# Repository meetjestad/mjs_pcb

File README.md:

Meetjestad PCB repository
=========================

This repository contains various versions of the sensor station PCB used
by [Meetjestad](https://www.meetjestad.net).

The easiest way to see the various version is to have a look at the
releases on Github, which are tagged with the version number. The
release pages also contain rendered (PDF) schematics and board files.

Software
--------
These boards can be programmed using the Arduino environment. The
necessary configuration and support files to allow this, along with
instructions can be found in the [mjs_boards
repository](https://github.com/meetjestad/mjs_boards).

The firmware typically used on these boards is published in the
[mjs_firmware repository](https://github.com/meetjestad/mjs_firmware)
(mjs2020 branch for the MJS2020 board).

License
-------
The original MJS sensor board is designed by Harmen Zijp, together with
Matthijs Kooijman. The MJS2020 board is partly based on the original
board and is designed by [KITT Engineering](https://www.kitt.nl/en/),
together with Harmen Zijp and Matthijs Kooijman.

The design for both boards is open hardware and licensed
under the the CERN-OHL-W v2 license. Any designs derived from or
containing parts of this design must be similarly licensed. See the
LICENSE file for the full license text.

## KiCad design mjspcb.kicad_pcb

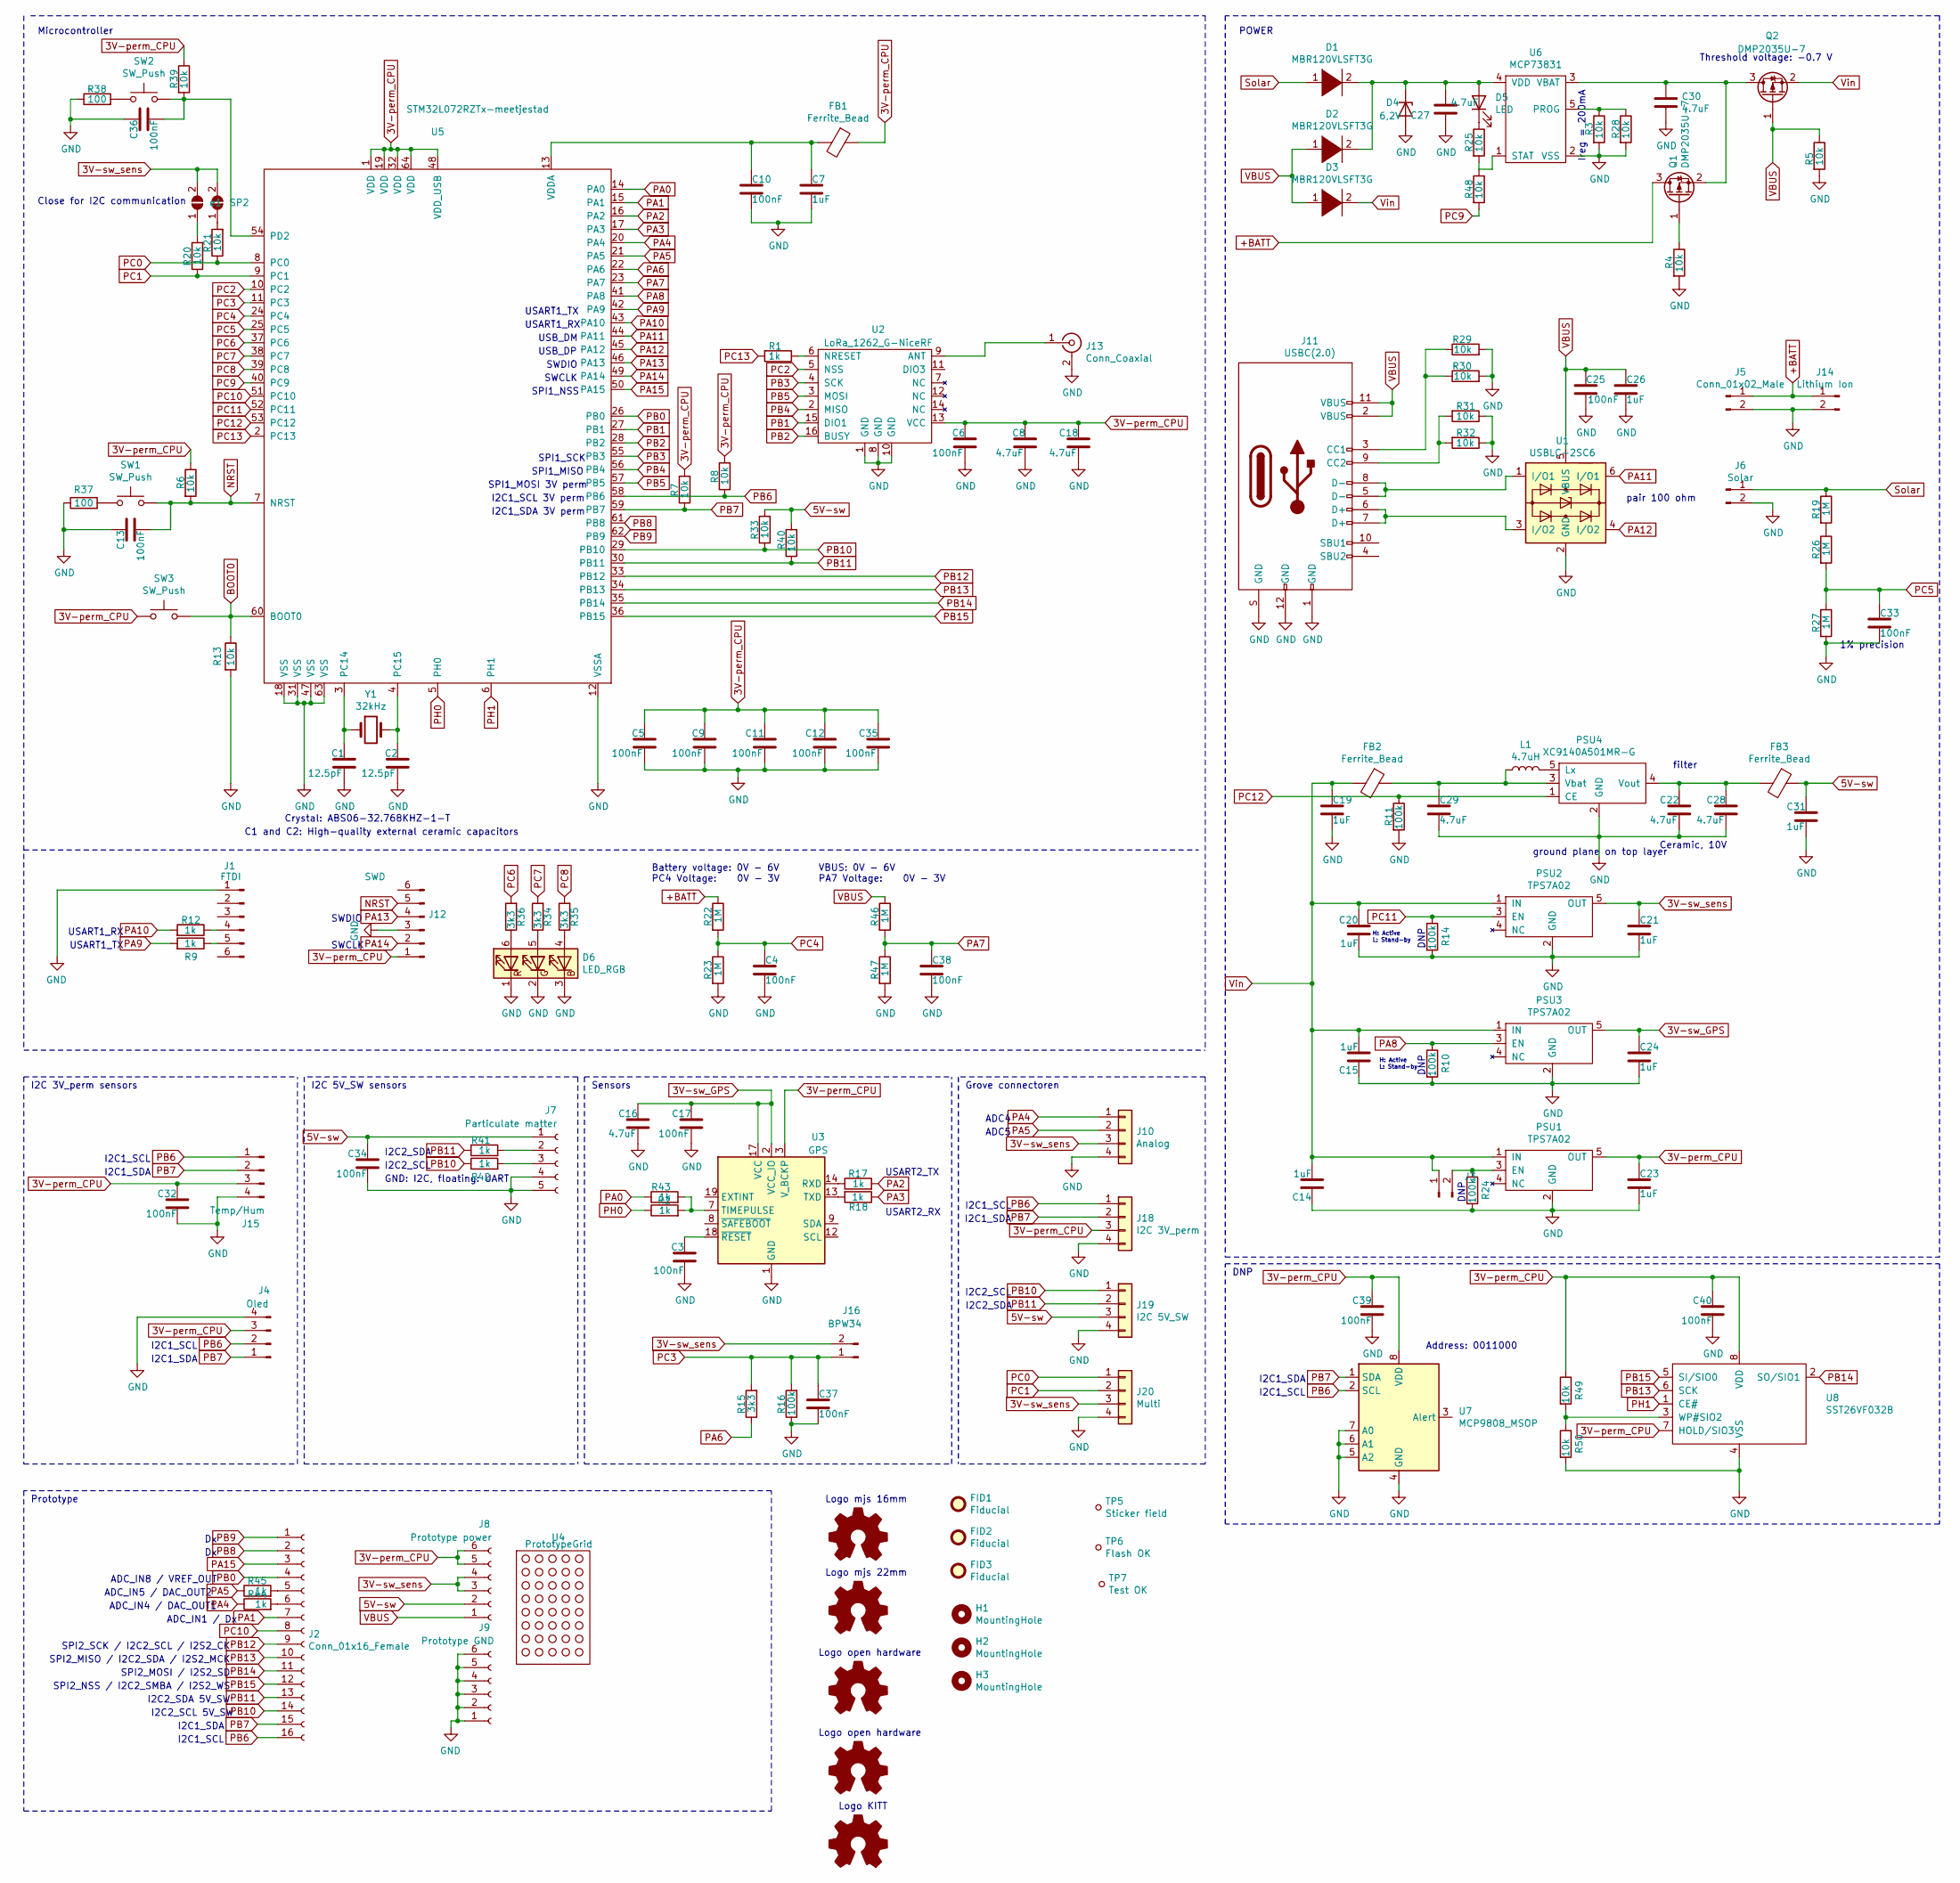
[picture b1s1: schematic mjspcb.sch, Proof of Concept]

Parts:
C1, C2: 12.5pF; C_0805_2012Metric_Pad1.15x1.40mm_HandSolder
C3, C4, C5, C6, C9, C10, C11, C12, C13, C17, C25, C32, C33, C34, C35, C36, C37, C38, C39, C40: 100nF; C_0805_2012Metric_Pad1.15x1.40mm_HandSolder
C7, C14, C15, C19, C20, C21, C23, C24, C26, C31: 1uF; C_0805_2012Metric_Pad1.15x1.40mm_HandSolder
C8, C16, C18, C22, C27, C28, C29, C30: 4.7uF; C_0805_2012Metric_Pad1.15x1.40mm_HandSolder
D1, D2, D3: MBR120VLSFT3G; Diode_SMD-SOD_123
D4: 6,2V; D_SOD-123
D5: LED; LED_0805_2012Metric
D6: LED_RGB; JTS3535
FB1, FB2, FB3: Ferrite_Bead; R_0805_2012Metric_Pad1.15x1.40mm_HandSolder
FID1, FID2, FID3: Fiducial; Fiducial_0.5mm_Mask1mm
H1, H2, H3: MountingHole; MountingHole_3.2mm_M3
J1: FTDI; PinHeader_1x06_P2.54mm_Vertical
J2: Conn_01x16_Female; PinHeader_Female_1X16
J3: Conn_01x02_Male; PinHeader_Male_1X2
J4: Oled; OLED_1.3
J5: Conn_01x02_Male; Battery__holder
J6: Solar; Combi_2.0_2.45pitch_2PIN
J7: Particulate matter; B5B-ZR
J8: Prototype power; PinHeader_Female_1X6
J9: Prototype GND; PinHeader_Female_1X6
J10: Analog; 2,54_2.0pitchCombi
J11: USBC(2.0); DX07S016JA3R1500
J12: SWD; PinHeader_1x06_P2.54mm_Vertical
J13: Conn_Coaxial; SMA connector edge mount
J14: Lithium Ion; Combi_2.0_2.45pitch_2PIN
J15: Temp/Hum; SI7021
J16: BPW34; PinHeader_Male_1X2
J18: I2C 3V_perm; 2,54_2.0pitchCombi
J19: I2C 5V_SW; 2,54_2.0pitchCombi
J20: Multi; 2,54_2.0pitchCombi
L1: 4.7uH; R_0805_2012Metric_Pad1.15x1.40mm_HandSolder
Logo_kitt1: Logo_Open_Hardware_Small; Kitt_logo
Logo_mjs1: Logo_Open_Hardware_Small; mjs-logo-16mm
Logo_mjs2, Logo_mjs4: Logo_Open_Hardware_Small; OSHW-Logo2_7.3x6mm_SilkScreen
Logo_mjs3: Logo_Open_Hardware_Small; mjs-logo-22mm
PSU1, PSU2, PSU3: TPS7A02; SOT-23-5_HandSoldering
PSU4: XC9140A501MR-G; SOT-23-5_HandSoldering
Q1, Q2: DMP2035U-7; SOT-23
R1, R2, R9, R12, R17, R18, R41, R42, R43, R44, R45: 1k; R_0805_2012Metric_Pad1.15x1.40mm_HandSolder
R3, R4, R5, R6, R7, R8, R13, R20, R21, R25, R28, R29, R30, R31, R32, R33, R39, R40, R48, R49, R50: 10k; R_0805_2012Metric_Pad1.15x1.40mm_HandSolder
R10, R11, R14, R16, R24: 100k; R_0805_2012Metric_Pad1.15x1.40mm_HandSolder
R15, R34, R35, R36: 3k3; R_0805_2012Metric_Pad1.15x1.40mm_HandSolder
R19, R22, R23, R26, R27, R46, R47: 1M; R_0805_2012Metric_Pad1.15x1.40mm_HandSolder
R37, R38: 100; R_0805_2012Metric_Pad1.15x1.40mm_HandSolder
SP2: SolderJumper_2_Open; SolderJumper-2_P1.3mm_Bridged_RoundedPad1.0x1.5mm
SW1, SW2: SW_Push; SW_Push_6mm
SW3: SW_Push; Switch_Header2.54_Combi
TP5: Sticker field
TP6: Flash OK
TP7: Test OK
U1: USBLC-2SC6; SOT-23-6_Handsoldering
U2: LoRa_1262_G-NiceRF
U3: GPS; GPS_ublox-SAM-M8Q
U4: PrototypeGrid; Prototype grid
U5: STM32L072RZTx-meetjestad; STM32F072_LQFP-64
U6: MCP73831; SOT-23-5_HandSoldering
U7: MCP9808_MSOP; MSOP-8_3x3mm_P0.65mm
U8: SST26VF032B; SOIJ-8_5.3x5.3mm_P1.27mm
Y1: 32kHz; R_0805_2012Metric_Pad1.15x1.40mm_HandSolder
e1: SolderJumper_2_Open; SolderJumper-2_P1.3mm_Bridged_RoundedPad1.0x1.5mm

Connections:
3V-perm_CPU: C5.1, C6.1, C8.1, C9.1, C11.1, C12.1, C18.1, C23.1, C32.2, C35.1, C39.2, C40.2, FB1.1, J4.3, J8.5, J8.6, J12.1, J15.3, J18.3, PSU1.5 (OUT), R6.1, R7.2, R8.2, R39.1, R49.1, SW3.1, U2.13 (VCC), U3.3 (V_BCKP), U5.1 (VDD), U5.19 (VDD), U5.32 (VDD), U5.48 (VDD_USB), U5.64 (VDD), U7.8 (VDD), U8.7 (HOLD/SIO3), U8.8 (VDD)
3V-sw_GPS: C16.1, C17.1, C24.1, PSU3.5 (OUT), U3.2 (VCC_IO), U3.17 (VCC)
3V-sw_sens: C21.1, J8.3, J8.4, J10.3, J16.2, J20.3, PSU2.5 (OUT), SP2.2 (B), e1.2 (B); also elsewhere on the board
5V-sw: C31.1, C34.2, FB3.1, J7.1, J8.2, J19.3, R33.2, R40.2
+BATT: J5.1, J14.1, Q1.3 (D), R22.1
BOOT0: R13.1, SW3.2, U5.60 (BOOT0)
GND: C1.2, C2.2, C3.1, C4.2, C5.2, C6.2, C7.2, C8.2, C9.2, C10.2, C11.2, C12.2, C13.2, C14.1, C15.1, C16.2, C17.2, C18.2, C19.2, C20.1, C21.2, C22.2, C23.2, C24.2, C25.1, C26.2, C27.1, C28.2, C29.2, C30.2, C31.2, C32.1, C33.2, C34.1, C35.2, C36.2, C37.2, C38.2, C39.1, C40.1, D4.2 (A), D6.1 (RK), D6.2 (GK), D6.3 (BK), J1.1, J4.4, J5.2, J6.2, J7.4, J7.5, J9.1, J9.2, J9.3, J9.4, J9.5, J9.6, J10.4, J11.1 (GND), J11.12 (GND), J11.S (GND), J12.3, J13.2 (Ext), J14.2, J15.4, J18.4, J19.4, J20.4, PSU1.2 (GND), PSU2.2 (GND), PSU3.2 (GND), PSU4.2 (GND), R3.2, R4.2, R5.2, R10.2, R11.2, R13.2, R14.2, R16.1, R23.2, R24.2, R27.2, R28.2, R29.2, R30.2, R31.1, R32.1, R37.1, R38.1, R47.2, R50.2, U1.2 (GND), U2.1 (GND), U2.8 (GND), U2.10 (GND), U3.1 (GND), U3.4 (GND), U3.5 (GND), U3.6 (GND), U3.10 (GND), U3.11 (GND), U3.15 (GND), U3.16 (GND), U3.20 (GND), U5.12 (VSSA), U5.18 (VSS), U5.31 (VSS), U5.47 (VSS), U5.63 (VSS), U6.2 (VSS), U7.4 (GND), U7.5 (A2), U7.6 (A1), U7.7 (A0), U8.4 (VSS)
NRST: C13.1, J12.5, R6.2, SW1.2, U5.7 (NRST)
unnamed: C1.1, U5.3 (PC14), Y1.1
unnamed: C2.1, U5.4 (PC15), Y1.2
unnamed: C3.2, U3.18 (~RESET)
unnamed: C7.1, C10.1, FB1.2, U5.13 (VDDA)
unnamed: C22.1, C28.1, FB3.2, PSU4.4 (Vout)
unnamed: C27.2, D1.2 (A), D2.2 (A), D4.1 (K), D5.2 (A), U6.4 (VDD)
unnamed: C29.1, FB2.1, L1.1, PSU4.3 (Vbat)
unnamed: C30.1, Q1.2 (S), Q2.3 (D), U6.3 (VBAT)
unnamed: C36.1, R39.2, SW2.2, U5.54 (PD2)
unnamed: D5.1 (K), R25.1
unnamed: D6.4 (BA), R35.1
unnamed: D6.5 (GA), R34.1
unnamed: D6.6 (RA), R36.1
unnamed: J1.4, R12.1
unnamed: J1.5, R9.1
unnamed: J2.5, R45.2
unnamed: J2.6, R44.2
unnamed: J3.2, PSU1.3 (EN), R24.1
unnamed: J7.2, R41.2
unnamed: J7.3, R42.2
unnamed: J11.3 (CC1), R29.1, R30.1
unnamed: J11.5 (D-), J11.8 (D-), U1.1 (I/O1)
unnamed: J11.6 (D+), J11.7 (D+), U1.3 (I/O2)
unnamed: J11.9 (CC2), R31.2, R32.2
unnamed: J13.1 (In), U2.9 (ANT)
unnamed: L1.2, PSU4.5 (Lx)
unnamed: Q1.1 (G), R4.1
unnamed: R1.1, U2.6 (NRESET)
unnamed: R2.2, R43.2, U3.7 (TIMEPULSE)
unnamed: R17.1, U3.14 (RXD)
unnamed: R18.2, U3.13 (TXD)
unnamed: R19.2, R26.1
unnamed 49: R20.2, e1.1 (A); also elsewhere on the board
unnamed: R21.2, SP2.1 (A)
unnamed: R25.2, R48.1, U6.1 (STAT)
unnamed: R3.1, R28.1, U6.5 (PROG)
unnamed: R37.2, SW1.1
unnamed: R38.2, SW2.1
unnamed: R49.2, R50.1, U8.3 (WP#SIO2)
PA0: R43.1, U5.14 (PA0)
PA1: J2.7, U5.15 (PA1)
PA2: R17.2, U5.16 (PA2)
PA3: R18.1, U5.17 (PA3)
PA4: J10.1, R44.1, U5.20 (PA4)
PA5: J10.2, R45.1, U5.21 (PA5)
PA6: R15.1, U5.22 (PA6)
PA7: C38.1, R46.2, R47.1, U5.23 (PA7)
PA8: PSU3.3 (EN), R10.1, U5.41 (PA8)
PA9: R9.2, U5.42 (PA9)
PA10: R12.2, U5.43 (PA10)
PA11: U1.6 (I/O1), U5.44 (PA11)
PA12: U1.4 (I/O2), U5.45 (PA12)
PA13: J12.4, U5.46 (PA13)
PA14: J12.2, U5.49 (PA14)
PA15: J2.3, U5.50 (PA15)
PB0: J2.4, U5.26 (PB0)
PB1: U2.15 (DIO1), U5.27 (PB1)
PB2: U2.16 (BUSY), U5.28 (PB2)
PB3: U2.4 (SCK), U5.55 (PB3)
PB4: U2.2 (MISO), U5.56 (PB4)
PB5: U2.3 (MOSI), U5.57 (PB5)
PB6: J2.16, J4.2, J15.1, J18.1, R8.1, U5.58 (PB6), U7.2 (SCL)
PB7: J2.15, J4.1, J15.2, J18.2, R7.1, U5.59 (PB7), U7.1 (SDA)
PB8: J2.2, U5.61 (PB8)
PB9: J2.1, U5.62 (PB9)
PB10: J2.14, J19.1, R33.1, R42.1, U5.29 (PB10)
PB11: J2.13, J19.2, R40.1, R41.1, U5.30 (PB11)
PB12: J2.9, U5.33 (PB12)
PB13: J2.10, U5.34 (PB13), U8.6 (SCK)
PB14: J2.11, U5.35 (PB14), U8.2 (SO/SIO1)
PB15: J2.12, U5.36 (PB15), U8.5 (SI/SIO0)
PC0: J20.1, R21.1, U5.8 (PC0)
PC1: J20.2, R20.1, U5.9 (PC1)
PC2: U2.5 (NSS), U5.10 (PC2)
PC3: C37.1, J16.1, R15.2, R16.2, U5.11 (PC3)
PC4: C4.1, R22.2, R23.1, U5.24 (PC4)
PC5: C33.1, R26.2, R27.1, U5.25 (PC5)
PC6: R36.2, U5.37 (PC6)
PC7: R34.2, U5.38 (PC7)
PC8: R35.2, U5.39 (PC8)
PC9: R48.2, U5.40 (PC9)
PC10: J2.8, U5.51 (PC10)
PC11: PSU2.3 (EN), R14.1, U5.52 (PC11)
PC12: PSU4.1 (CE), R11.1, U5.53 (PC12)
PC13: R1.2, U5.2 (PC13)
PH0: R2.1, U5.5 (PH0)
PH1: U5.6 (PH1), U8.1 (CE#)
Solar: D1.1 (K), J6.1, R19.1
VBUS: C25.2, C26.1, D2.1 (K), D3.1 (K), J8.1, J11.2 (VBUS), J11.11 (VBUS), Q2.1 (G), R5.1, R46.1, U1.5 (VBUS)
Vin: C14.2, C15.2, C19.1, C20.2, D3.2 (A), FB2.2, J3.1, PSU1.1 (IN), PSU2.1 (IN), PSU3.1 (IN), Q2.2 (S)

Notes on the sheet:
Microcontroller
C1 and C2: High-quality external ceramic capacitors
Crystal: ABS06-32.768KHZ-1-T
USART1_TX
USART1_RX
SPI1_NSS
SPI1_MISO
SPI1_SCK
USB_DP
USB_DM
SWDIO
SPI1_MOSI 3V perm
I2C1_SCL 3V perm
USART2_TX
USART2_RX
SWCLK
GND: I2C, floating: UART
ADC4
ADC5
Grove connectoren
I2C 5V_SW sensors
I2C2_SDA
I2C 3V_perm sensors
I2C1_SDA 3V perm
I2C1_SCL
I2C1_SDA
I2C2_SCL 5V_SW
I2C2_SDA 5V_SW
I2C2_SCL
ADC_IN1 / Dx
ADC_IN5 / DAC_OUT2
ADC_IN4 / DAC_OUT1
SPI2_MOSI / I2S2_SD
Logo mjs 16mm
Logo open hardware
Logo KITT
Battery voltage: 0V - 6V PC4 Voltage: 0V - 3V
Prototype
Sensors
pair 100 ohm

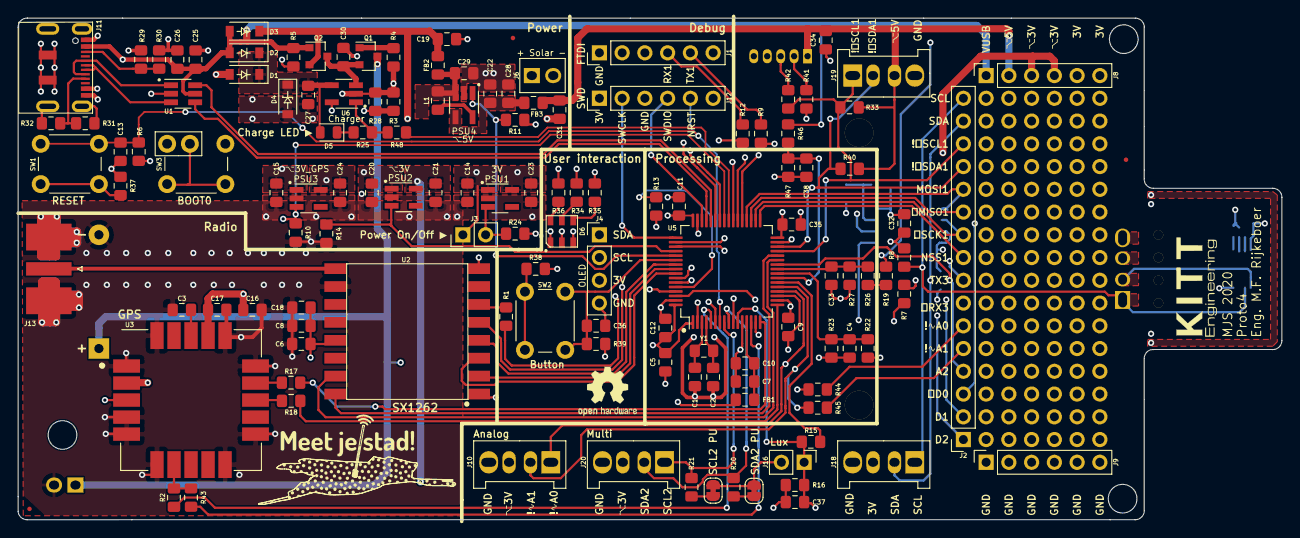
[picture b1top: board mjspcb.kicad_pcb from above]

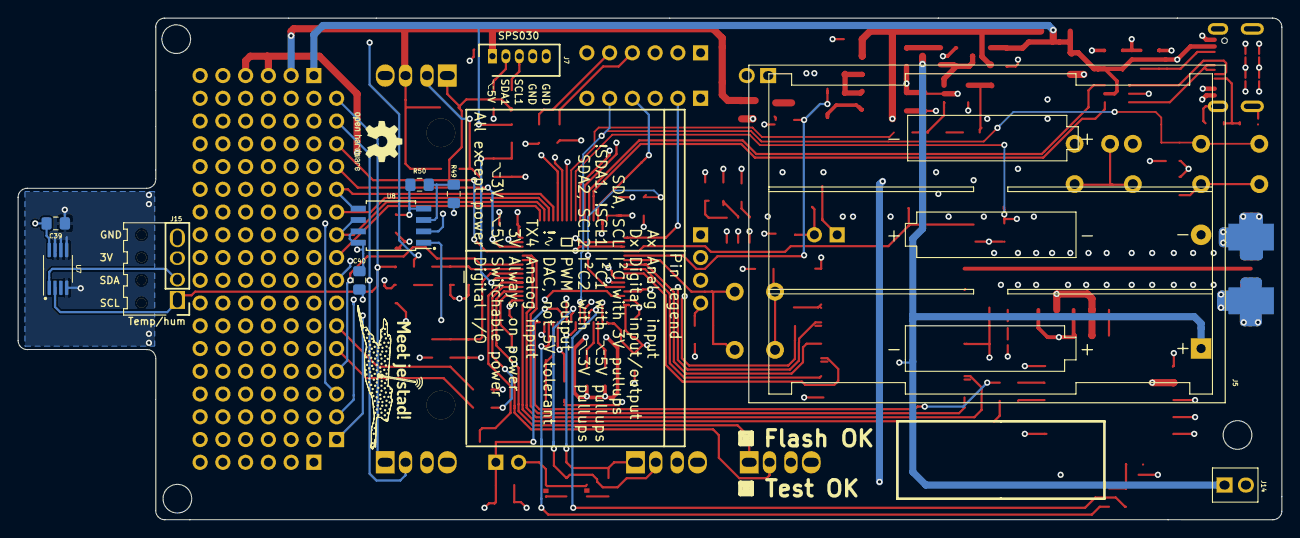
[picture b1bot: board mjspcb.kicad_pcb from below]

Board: 4 copper layers, 141.1 x 56.0 mm, 153 parts (15 on the bottom side), 98 nets.

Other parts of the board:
SP1: SolderJumper_2_Open; SolderJumper-2_P1.3mm_Bridged_RoundedPad1.0x1.5mm

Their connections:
3V-sw_sens: SP1.2; also elsewhere on the board
unnamed 49: SP1.1; also elsewhere on the board

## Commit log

2017-11-07 Revision 2 of Meet je stad PCB
    *added reset header
    *changed pinout of I2C breakout to accomodate Sparkfun Si7021
    *various minor other modifications
2017-11-07 Updated pdf files for PCB revision 2
2018-12-18 Remove build products
    This removes the gerbers, rendered schematics and bom (in various
    format). These will be outdated during development and only really
    relevant for released version, so they are probably better put in a
    release on github rather than in git.
2018-12-18 Convert schematic to KiCad 5
    In KiCad 5, symbols reference the library they are in explicitly. Also,
    a lot of symbols were changed for more consistency. This commit changes
    all symbols to their new version in the official libraries, removing the
    need for our own symbol library (which is removed by this commit).
    For the STU MOSFET component, not specific symbol is available, so a
    generic MOSFET symbol is used instead.
2018-12-18 Delete netlist
    There is no real reason to keep this in git, it is just a temporary file
    between the schema and the layout.
2018-12-18 Replace 2-pin sensor connectors with KK254
    These are latching, polarity protected connectors. This mostly changes
    to silkscreen, though the pads are also slighly differently sized.
2018-12-18 Run a track & via cleanup
2018-12-18 Convert board layout to KiCad 5
    This replaces all footprints with new versions from KiCad 5. Some
    positions and labeling as changed, so this updates everything to match
    the original layout for the most part. Some footprints (barrel jack,
    regulator, battery holder, solder jumpers, perfboard "connector") are
    slightly different. In particualr the battery holde slightly changes the
    mounting hole position and size, so this might need to be changed back
2018-12-18 Fix schematic for reset connector
    In the schematic, the reset pin header was connected to the reset pin in
    the serial header, on the far side of the reset capacitor. However, in
    the board layout, it was connected on the near side of the capacitor,
    directly to the MCU pin. This reflects that.
2018-12-18 Flip I²C socket
    This swaps the pin numbering, to match the Grove pinout. The PCB layout
    is also updated to flip the footprint, and move a few traces to make
    room for the square pad on the other side.
2018-12-18 Add DC plug and Lipo connector to schematic
    These were in the board layout, but not in the schematic. This adds them
    to the schematic, and sets the appropriate references in the layouted
    footprints.
    Note that the DC plug symbol has a different pin numbering than the
    footprint currently in use, but the symbol does match the footprint set
    in the schematic, so this should work out when the netlist is re-read in
2018-12-18 Remove unused footprint libraries
    The libraries referred to are not present in git and are unused, so
    remove them to prevent warnings when loading footprints.
2018-12-18 Replace I²C connector with a more sturdy one
    This one has extra holes to plug in the sensor, so it can be mounted
    lower and more stable. This also makes the board slightly longer at the
    bottom to accomdate the new connector, and shorter at the top.
2018-12-18 Add mounting holes and logos to the schematic
    This adds them and sets footprints, but does not update the board (not
    even to update the REF properties, since I had too many other changes
    already).
2018-12-18 Increase board size
    This increases the width to 56mm, so it no longer needs extra plates to
    fit into the housing. The length is also slightly increased (to make
    room to mount the GPS antenna later), but kept within 100mm (which makes
    prototype PCBs a lot cheaper with some suppliers).
2018-12-18 Add .gitignore file
2018-12-18 Add slot for GPS
    This also moves the barrel jack and LiPo connectors to make room for the
    slot, and removes some of the ground plane to prevent interfering with
    the GPS and LoRa antenna.
2018-12-18 Fix input voltage range on silkscreen
    This changes the minimum to 3.6V, which should be safe. The MCP1700
    datasheet has a dropout voltage of 178mV typical, 350mV max (at 250mA).
    Given we need a lower current, calculating with a 300mV dropout seems
    ok.
2018-12-18 Move reset header to fix connections
    This was accidentally disconnected when introducing a keepout zone for
    the antennas recently.
2018-12-18 Fix DRC errors in solder jumper footprint
    This uses a modified solder jumper footprint that has a graphic polygon
    rather than overlapping pads to connect the default pins, which prevents
    DRC errors. See: https://github.com/KiCad/kicad-footprints/issues/1165
2018-12-18 Improve I²C connector
    This removes the plating from the second row of holes, updates the
    footprint metadata and reroutes a trace around it to prevent a DRC
    violation.
2018-12-18 Re-add battery compartment
    This was accidentally removed two commits ago.
2018-12-18 Merge text under OSHW logo in one element
    Each of three lines were separate text objects, but you can also just
    use newlines in a single text object.
2018-12-18 Bump version and copyright year
2018-12-18 Add extra connectors to the board
    This adds two connectors for dust sensors (SDS011 and HPMA115S0-XXX) and
    two more generic grove connectors (digital and I²C). It also adds a long
    pin header with assorted connections (I²C, SPI, various power) for use
    with a piggy-back additional PCB which is expected to handle more
    complex power needs.
    For the grove connectors, some custom experimental footprints are added
2020-10-11 Add README and license
2020-10-11 Link to kitt board files for the MJS2020 board
2020-10-11 Replace with MJS2020-PROTO2 redesign
2021-03-01 Convert project file and symbol library to unix line endings
2021-03-01 Update to MJS2020-PROTO3
    See CHANGELOG.md for detailed changes.
2021-05-21 Update to MJS2020-PROTO4
2021-05-21 Add SVG of MJS logo
    This is the original svg that was used to generate the logo footprints,
    see the description of the footprints for the command that was used.
2021-05-21 Add spreadsheet with pin assignments
2021-05-21 Update README links to core and firmware
2023-08-10 Update crystal and load caps
    Turns out the type number in the schematic was not actually used, but
    the ABS06-32.768KHZ-7 was used instead (which better matches the load
    capacitors chosen).
